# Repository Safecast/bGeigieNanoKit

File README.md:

## bGeigie Nano Kit Operating Instructions (Updated March 2025)

# Table of Contents

1.  [Introduction](#introduction)
2.  [Powering the Device On](#powering-the-device-on)
3.  [Switching Between Modes](#switching-between-modes)
4.  [Measuring Ionizing Radiation in Logging Mode](#measuring-ionizing-radiation-in-logging-mode)
5.  [Measuring Ionizing Radiation in Surface Mode](#measuring-ionizing-radiation-in-surface-mode)
    1. [Alarm](#alarm)
    2. [Data Log](#data-log)
6.  [Uploading Data to the Safecast Database With the Safecast API](#uploading-data-to-the-safecast-database-with-the-safecast-api)
7.  [Uploading Data to Other Datasets](#uploading-data-to-other-datasets)
8. [Using Safecast With Mobile Apps](#using-safecast-with-mobile-apps)
9. [Troubleshooting](#troubleshooting)
    1. [Troubleshooting the iSafecast Geiger Bot App for iOS](#troubleshooting-the-isafecast-geiger-bot-app-for-ios)
    2. [Troubleshooting the iSafecast Geiger Bot App's API](#troubleshooting-the-isafecast-geiger-bot-apps-api)
    3. [Troubleshooting Other Issues](#troubleshooting-other-issues)
        1. [Firmware](#firmware)
    4. [Cleaning](#cleaning)
10. [Warranty Information](#warranty-information)
11. [Hardware Cautions](#hardware-cautions)
12. [Resources and Support](#resources-and-support)

## Introduction
The Safecast bGeigie Nano kit is a *geo-tagged mobile sensor of ionizing radiation*. It is equipped with Internet data sharing capability and optional wireless capability. 

The term "radiation" refers to energy emitted by a source. This includes light, heat, microwaves, and other types of energy. Ionizing radiation is a type radiation that has so much energy that it removes electrons from the atoms and molecules that make up air, water, and living tissue. This activity can harm the molecules in our bodies, leading to diseases like cancer. Radiation can come from either natural or human-made sources. Natural sources include radioactive rocks, elements, and a radioactive gas called radon. Human-made sources include nuclear power plants and medical diagnostic tests, such as x-rays.

The bGeigie Nano measures alpha, beta, and gamma radiation. 

| Type | Description |
| ---- | ----------- |
| Alpha Radiation | Alpha particles are charged particles that have a large mass and charge. As a result, they don't penetrate materials as easily as other types of ionizing radiation. They also don't travel very far. |
| Beta Radiation | Beta particles are similar to electrons. They are lighter than alpha particles and travel farther, up to a few feet through air. |
| Gamma Radiation | Gamma particles are the most powerful form of ionizing radiation. They travel very far at the speed of light and penetrate most materials easily. Thick layers of concrete, lead, steel, or similar materials are required to stop gamma particles. |

The Nano's maximum operating range is about 350,000cpm, or 1mSv/h (1 millisievert per hour dose rate or 1000µSv/h microsieverts per hour). 

The Nano can be mounted on a car window, or used for static or spot radiation detection. Nano users can submit their mobile radiation measurements to Safecast, an online global mapping system developed by Safecast and MIT Media Lab. 

The Nano also records location, date, and time. The location data allows Safecast to map the measurements and understand the distribution of ionizing radiation. Safecast uses the date and time information to track how ionizing radiation concentrations change over time. The do-it-yourself kit enables customization, cost savings, and learning. 

## Powering the Device On

To turn the unit on, slide the switch at the lower right to the up position. 

The SAFECAST logo will appear on the display for approximately one second. The next start-up screen displays the name of model (bGeigie Nano), the firmware version number, battery charge level, basic settings, and the user’s name (or other customizable information).  

## Switching Between Modes

* The bGeigie Nano has two operating modes, "display" and "recording". To alternate between them, use the toggle switch at the upper right. Label on the transparent top panel: (to the right) "bq/m^2; uS/h", (to left) "log; cpm".

+ The “up” position (to the right) switches the unit into display mode (in which there is no data logging). The fields on the OLED indicate uSv/h dose-rate (Cs137), max dose-rate, dosimeter, Bq/m2 display (Cs137), time stamp, and alarm. 

+ The “down” position puts the Nano into recording mode. The OLED shows indicators for CPM and µSv/h, the number of satellites locked, altitude (meters), distance traversed (km), total duration of measurement (h:m), and time stamp (dd:hh:mm:ss). When the Nano is in recording mode, the OLED shows whether a micro-SD memory card is currently inserted. 

## Measuring Ionizing Radiation in Logging Mode

While in recording mode, the OLED display also shows a GPS lock indicator. When the device locks onto a GPS signal, it will show the number of satellites found, and a small red LED will glow. If the device isn't getting a lock, try placing it near a window for a few minutes.

The small red LED will only glow if the GPS is locked, the SD card is present, the battery has more than 10% charge left, the unit has been on for one minute, and the Geiger tube is providing a pulse. It can be dimmed by setting DIP switch #2 to "Off."

The speaker "clicks" and a small blue LED blinks with each pulse from the Geiger tube. It can be dimmed by setting DIP switch #1 to "Off."

The red LED on the GPS unit blinks every 1 second when the GPS is not locked. Once locked, it blinks every 10 seconds.

The date and time are in __UTC__ (formerly called GMT), rather than local time. The __date/time stamp__ refreshes when log data is written to the card. The LOG's file name is based on the time stamp   (e.g., 21080716.LOG).  The UTC log filename may be +/- one day off from the local date of the measurement, depending on the difference between time zones and distance from the International Date Line (IDL). The file metadata is not updated, which means the log's file creation date may appear with a default date, such as 01/01/2000. For this reason, we recommend that you sort your logs by filename instead of the date field.  When uploading a log, please enter its metadata in the required fields, and submit it for approval. 

**GPS Reset Procedure** (ver 1.3.0 and later)

To reset the GPS device: 

1) Turn off the bGeigie
2) Remove the SD card
3) Turn the bGeigie back on and leave it on for one minute 

    After approximately 10 seconds, the display will show the message "NO SD CARD/GPS Reset." Note that powering the unit on without the SD card will cause an error and **re-initialize the unit, including the GPS controller**.

4) Turn the device off again
5) Insert the SD card

## Measuring Ionizing Radiation in Surface Mode

Use surface mode to detect surface contamination. Removing the Nano from its case while in surface mode can increase the Nano's ability to detect alpha and beta radiation.

1. Remove the Nano from its case (with or without the rubber liner). Use both thumbs to push the unit in and then swivel it out. When you reinsert the Nano into the case later on, you can do it either above or inside the removable rubber liner.

While in uSv/Bq mode, the display also shows the peak dose rate (in uSv/h), total accumulated dose (in uSv), and CPM. 

The mode switch sets the bGeigie Nano into "Log Mode" (switch down "log cpm"). In Log Mode, the largest area of the display ("the big numbers") shows the count rate in CPM, and data will be written to the SD card.  In "Survey Mode" (switch up "Bq/m2 uSv/h"), the main part of the display will show the dose rate in microsieverts per hour.

- To measure the uSv dose rate accurately, put the Nano in the case, hold it 1m above the ground, tilt it around 45 degrees, and then wait for approximately one minute for a stable reading.

- To measure bQ accurately, take the Nano out of the case, keep it within 5cm to 1cm from the surface, and wait approximately one minute for a stable reading. Then, read the value on the second line in Bq/m2. The Nano will emit a speaker sound to aid in finding hotspots.

- The dose rate is based on the assumptions that the Nano is in its case; it is about 1 meter (3ft) away from any object or surface; any gamma rays are of moderate energy (600~700KeV); and the unit has met the previous conditions for at least one minute.

- Also in Survey Mode, the second line on the display ("the small numbers") will rotate through several other values. One of those will be Bq/m2. That is only a locally displayed interpretation of the data, and requires very different conditions to be correct: the Nano is _out_ of its case and held 1cm (~half inch) from a surface contaminated with radio cesium. This usage probably only works in Fukushima and Chernobyl.

### Limitations  

The grid on the pancake sensor is only useful when you remove the unit from the case to look for surface contamination. The grid itself has a very small shielding effect, mostly for alpha/beta and weak gamma radiation. The effect is minimal, and can be ignored.

When averaging readings from two different Nanos, you should only compare long-term counting (e.g. number of counts for 10 minutes).
 
### Alarm
- A speaker "clicks" and a small blue LED “Count” blinks with each pulse from the Geiger tube. It can be dimmed by setting DIP switch #1 to "Off."
- A small Red LED “Log/Alarm” flickers on pulse, and remains lit on alarm. It will only glow if the GPS is locked, the SD card is present, the battery has more than 10% charge left, the unit has been on for one minute, and the Geiger tube is providing a pulse. It can be dimmed by setting DIP switch #2 to "Off."
- The Piezo buzzer may not loud enough for all users. There are solder pads available on the Nano main board for an optional audio-out connector that can be used to connect an amplifier or sound recorder to get louder clicks, if desired.

### Data Log

In recording mode, the data log file writes to the micro-SD card. A key to the fields in the Data Log is available in the [bGeigie library README.md by fakufaku](https://github.com/Safecast/SafecastBGeigie). 

The data is formatted similarly to the NMEA sentences that GPS uses. It begins with a dollar sign ($) and ends with an asterisk (*). A checksum follows the star.

>Radiation Data Sentence: This is the basic message containing the geo-located radiation measurement.

>EXAMPLE:

>$BNRDD,300,2012-12-16T17:58:31Z,30,1,116,A,4618.9612,N,00658.4831,E,443.7,A,5,1.28*6D

**KEY**

| Field | Description | Example|
| ----- | ----------- | ---- |
| Header   | the device model header | Mini=BMRDD, Nano=BNRDD, NX=BNXRDD |
| Device ID | the device serial number | 300 |
| Date  | the date, formatted according to the ISO-8601 standard, usually in UTC | 2012-12-16T17:58:31Z |
| Radiation 1 minute  | the number of pulses given by the Geiger tube in the last minute | 30 |
| Radiation 5 seconds  | the number of pulses given by the Geiger tube in the last 5 seconds | 1 |
| Radiation total count   | the total number of pulses recorded since startup |  116  |
| Radiation count validity flag  | 'A' indicates the counter has been running for more than one minute, and the one-minute count is not zero. Otherwise, the flag is 'V' (void) | A |
| Latitude | as given by GPS; the format is ddmm.mmmm, where dd is decimal degrees and mm.mmmm is decimal minutes |  4618.9612 |
| Hemisphere |  'N' (north), or 'S' (south) | N |
| Longitude | as given by GPS; he format is dddmm.mmmm where ddd is decimal degrees and mm.mmmm is decimal minutes | 00658.4831 |
| East/West | 'W' (west) or 'E' (east) from the Prime Meridian | E |
| Altitude |  the altitude (above sea level), as given by the GPS, in meters | 443.7 |
| GPS validity | 'A' = Available or OK, 'V' = Void or invalid | A |
| Number of satellites | the number of satellites used by the GPS | 5 |
| HDOP | the Horizontal Dilution of Precision (HDOP), or relative accuracy of the horizontal position | 1.28 |
|Checksum |  | *6D |

*(For possible updates, see the current [README.md](https://github.com/Safecast/SafecastBGeigie/blob/master/README.md) in the technical GitHub repository)*

The data log file name is comprised of three parts: The DID number, the month the log was initiated, and the day the log was initiated. For example, "21080716.LOG" is the data log for unit 2108 from 16 July. Due to space constraints, the file date property is 01/01/2000. However, every line has UTC time date stamp reading.  The log file name may appear to be a day off due to time zone differences.

A data log or section begins with several comment lines, which begin with hash signs (#).

EXAMPLE:

>\# NEW LOG

>\# format=1.2.9nano

>\# deadtime=on

>$BNRDD,2108,2013-12-06T13:03:58Z,22,2,115,A,3145.7607,N,03510.1975,E,734.90,V,3,908*64

One of the comment lines contains the deadtime. [Deadtime](http://en.wikipedia.org/wiki/Dead_time) is "the time after each event during which the system is not able to record another event."  You can find the *ENABLE_LND_DEADTIME compensation formula* in the [bGeigieNano.ino master repository](https://github.com/Safecast/bGeigieNanoKit/blob/master/src/bGeigieNano.ino). 

### Uploading Data to the Safecast Database With the Safecast API

Your device is designed to submit data to the Safecast database through the Safecast API. To enable data submission, you’ll need to obtain an API key. The key is a credential that gives you access to the API, much like a username and password give you access to an email account.

You can [register on the Safecast site](https://api.safecast.org/en-US/users/sign_up) to get an API key. 

You can learn about how the Safecast API works by visiting the [API documentation](https://api.safecast.org/).

### Uploading Data to Other Datasets

Nano data can be submitted to other radiation mapping datasets. For example, the free [Geiger Bot iOS app](https://sites.google.com/site/geigerbot/) allows you to upload data to servers other than the [Safecast API dataset](https://api.safecast.org/). To do so, you'll need to configure the app with the details of your device, the particular sensor, data format, connection, and other information.  

### Using Safecast With Mobile Apps 

The official (currently not availble)[Safecast app for iOS](https://itunes.apple.com/us/app/safecast/id571167450?mt=8) brings our extensive dataset of radiation measurements to your mobile device, and provides a full toolset to help you perform measurements with your own instrument such as a Geiger or scintillation counter (not included). The app functions as a virtual Geiger counter, allowing you to see your location on a map while displaying radiation readings that have been taken nearby. The app is currently for iOS only. 

In addition, the Safecast Drive app [Android](https://github.com/Safecast/bGeigie-Drive) enables you to:

- Connect with your bGeigieNano (if you have the [bGeigeCast](https://bgeigiezen.safecast.jp/store-2/bgeigiecast-build-for-bgeigienano/) module installed), record data, and upload the data to Safecast directly, without removing your MicroSD card
- Access previous logs and update their status

**Common Issues**

1. Wrong cable - A "null modem" cable that swaps wires internally may cause problems. The cable should be straight/passthrough.
2. Input voltage too high - Interferes with the audio route and the audio engine's watchdog timer.
3. Mic-ground in the cable not shorted correctly - The app will report an audio route change to "Headphones" on the console. The audio route required for a line input cable is "Headset."

>>Nick Dolezal is working hard on the new version of the Safecast app (which will allow on demand refreshing of the map data) decided to whip up these alternate visualizations of the Safecast data. These maps show the frequency of samples taken – NOT READINGS OF THOSE SAMPLES – just showing how often a specific place has been measured. In this example, a location (like Fukushima) that has been measured repeatedly would show hot. Thought this was a really interesting look at the work Safecast has done over the last 2+ years

#### Troubleshooting the iSafecast Geiger Bot App's API

On the main numeric display of the app, you can tap on the top part of the screen to show detailed log messages containing information on connection attempts, and which input device is selected. If successful, the API upload will return HTTP 201 CREATED.

**Verify Input**

1. Tap the min/max arrow button in the lower-right hand corner of the map to resize it into a small window. The interface will display fixed buttons at the bottom, and four possible display screens at the top. These four screens are "Main Numeric Display," "CPS/CPM graph," "Audio input monitor graph," and "Map."

2. Tap the "<" button next to the white page dots under the map. The audio input monitor will appear.

3. Verify that the counts from the Onyx appear and that they're correct. The black line represents the input. The stationary red line represents the threshold the input volume must exceed for it to be counted. The black line will appear blue when it has been counted as a pulse.

If you're unable to verify input, you may have a defective serial cable. A "Geiger Pulse" setting on the Onyx of other than the default value of 6 may also cause problems. 

4. Configure the App's Settings

a. Tap the "Settings" icon on the fixed button panel (the machine gear). Scroll to the bottom of the list and select "Safecast."
b. Enter your API key. Change the upload interval as desired, but do not change the Safecast device back to Nano. 

#### Troubleshooting Other Issues

If you experience problems with the display, check all solder joints carefully to verify that you haven't missed a joint, or that you don't have a cold solder joint. These issues can cause the display to act unpredictably.

You can report bugs and other issues at the [issues page](https://github.com/Safecast/bGeigieNanoKit/issues) of the Safecast GitHub repository. Volunteer users report problems and bugs in the devices discussion group. 

##### Firmware
* For the current version of the firmware, see the the .hex file in the [bGeigieNanoKit repository](https://github.com/Safecast/bGeigieNanoKit).

* To learn how to update the firmware of the Fio via FTDI, see the ["How to Update the Firmware" page](https://github.com/Safecast/bGeigieNanoKit/wiki/How-to-Update-the-Firmware) of this wiki.

### Cleaning

To clean the unit:

1. Remove the Nano from the case. Never wet the Nano's interior. 
2. Use a soft brush and air blower on the Nano, carefully. A vacuum may be another option (electronics labs use unheated air blowers for dusting off parts.)
3. Rinse the liner in clean water, if necessary. 
4. The case may be rinsed with a clean, slightly damp microfiber cloth. 
5. Turn the screen display off and wait until it's cool before wiping the LEDs. Wipe the screen using light pressure.  Use clean, lint-free cotton, microfiber cloths or low-lint wipes. 

### Warranty Information

For warranty information, email [contact@safecast.org](contact@safecast.org). 

**Calibration** 

“The sensor is pre-calibrated. The calibration of the unit for Bq for Cs assumes the grid is in front of the pancake. The difference is around 5%. For gamma only, the grid has a negligible effect on the measured value.

The uSv/h conversion from CPM is calibrated assuming the grid is on the tube. As all Safecast measurements are done with the pancake WITH grid, please keep the grid on the tube. The grid itself will not block alpha or beta radiation, but will reduce the sensitivity slightly, as the grid covers a small portion of the sensor. In practice, the difference with and without grid will be around 4-5% for a beta source, and less for a gamma source, according to bGeigie Nano user Jam.

The software we have preloaded on the device takes the sensor type into account and calibrates readings for Cs137. All bGeigie Nanos have the same configuration and can be compared against one other. A bGeigie Nano's calibration should never change, unless the device is broken. 

### Hardware Cautions

- The Pelican micro case is shockproof and water-resistant. However, it is not waterproof and it cannot be used underwater. Condensation can build up inside the case, due to temperature differences. While this condensation will evaporate with time, you can also remove it by opening the unit and drying it with fiber-free cloth. 

- Do not use the unit outside of its water-resistant case with wet hands, in the rain, or close to a dripping tap. 

- The Micro-SD cannot be read through a USB port. Use a micro-SD card reader instead.

**Battery Cautions:** 

Charge the unit with the mini-USB cable. The yellow LED will dim once the unit is fully charged. A full charge takes 5-6 hours. The bGeigie Nano runs approx 35-40 hours on a full charge in recording mode. 

The main battery indicator is the icon at the bottom right of the display. The percent of battery charge appears on the startup screen.

**NEVER charge the bGeigie while the unit is on.** The power MUST be turned OFF before charging to avoid permanent damage to the charge circuit. 

+ Replace a broken battery (that has a detached wire) with one that has the same rating (2000mAh 3.7V Lithium Polymer (Li-Po, Li-Poly). The Nano charge circuit may overheat if you use a larger battery.

+ A Li-Po battery can be hazardous if the mylar membrane is punctured. Please handle batteries carefully! 

**SENSOR Cautions:**

Although the Nano sensor inside its closed Pelican micro-case is well protected from shock and pressure transients, sudden changes in pressure (such as slamming a car door) may damage the sensor. The pressure inside the tube is very low, and the membrane is under constant tension from atmospheric pressure. Being at altitude *reduces* the strain on it. Because the membrane is mica (basically extremely thin glass), it is low-density and very brittle. A sharp shock can shatter it, and it will pop if something pokes it. 

- To avoid damage to the pancake sensor, NEVER touch the membrane! 

**Onyx Hardware Precautions:**

To keep the Onyx™ in good condition, handle it with care, and observe the following precautions:

- Do not contaminate the Onyx™ by touching it to radioactive surfaces or materials. Instead, hold it just above the surface that is suspected of contamination to take readings. 

- Do not leave the Onyx™ in temperatures over 122° F (50° C), or in direct sunlight for extended periods of time. 

- If the surface of the mica on your pancake detector becomes scratched or loses its coating, avoid making measurements with the detector window in direct sunlight, as this could affect the readings. 

- Do not put the Onyx™ in a microwave oven. It cannot measure microwaves, and you may damage it or the oven. 

#### Resources and Support

- [Nano catch-all landing page](https://safecast.org/bgeigie-nano/)

- [Safecast website](https://safecast.org/) - articles, news, notices, API uploads, crowdsourced radiation data and maps, and more

- [Safecast Devices Discussions and Support group](https://groups.google.com/forum/?hl=en#!forum/safecast-devices)

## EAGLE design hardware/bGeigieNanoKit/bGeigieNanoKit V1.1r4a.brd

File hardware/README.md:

# HW development for bGeigieNanoKit has moved
## New V1.0r4 boards eagle files are in bGeigieNanoKit v1.0r4 folder 
## Older development can be found here [SafecastEagleHW] (https://github.com/Safecast/SafeCastEagleHW)

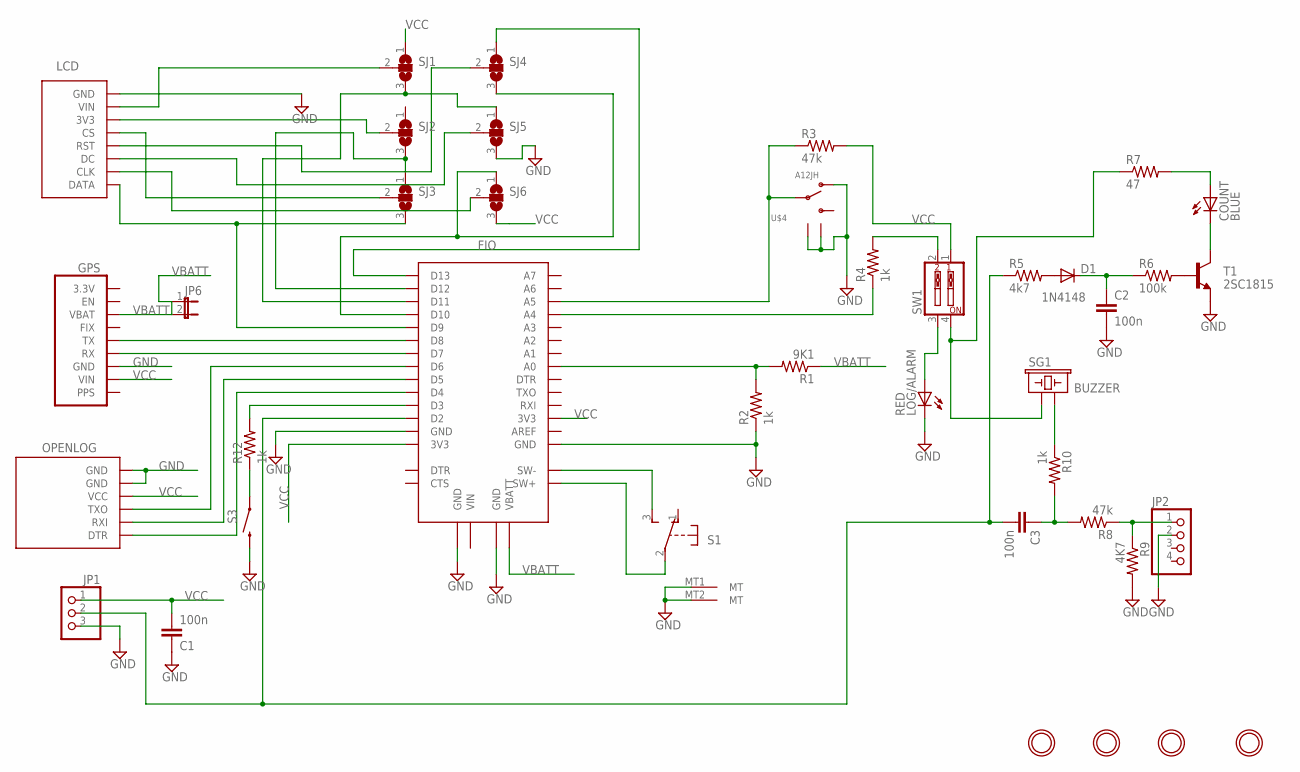
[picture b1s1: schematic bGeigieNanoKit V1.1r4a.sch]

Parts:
C1, C2, C3: 100n; C025-024X044
COUNT: BLUE; LED3MM
D1: 1N4148; DO35-7
FIO: FIO_SOCKETBOT; FIO_V23_SOCKET_BOT
GPS: ULTIMATE_GPSTOP; ULTIMATE_GPS_V3_TOP
JP1: PINHD-1X3/90; 1X03/90
JP2: HEADER-1X4ROUND; 1X04_ROUND
JP6: JUMPER-2SMD-NC; SJ_2S
LCD: SSD1306_128X64_V2_LCD1.3IN_LEVER; SSD1306_128X64_1.3IN_LCD_LEVER
LOG/ALARM: RED; LED3MM
OPENLOG: OPENLOG
R1: 9K1; 0207/10
R2, R4, R10, R12: 1k; 0207/10
R3, R8: 47k; 0207/10
R5: 4k7; 0207/10
R6: 100k; 0207/10
R7: 47; 0207/10
R9: 4K7; 0207/10
S1: S1; EG1206
S3: SWITCH-MOMENTARY-2PTH; TACTILE-PTH
SG1: BUZZER; BUZZER-12MM
SJ1, SJ2, SJ3, SJ4, SJ5, SJ6: SJ2W; SJ_2
SW1: SW_DIP-2; EDG-02
T1: 2SC1815; TO92-ECB
U$4: A12JH; A12AH
U$6, U$7, U$8, U$9: MOUNTINGHOLE3.0THIN; MOUNTINGHOLE_3.0_PLATEDTHIN

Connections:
GND: C1.1, C2.2, FIO.JP1$2 (GND), FIO.JP2$1 (GND), FIO.JP5$1 (GND), FIO.JP6$1 (GND), GPS.JP1$3 (GND), GPS.U$8$P$1 (GND), GPS.U$9$P$1 (GND), JP1.3, JP2.2, LCD.JP1$8 (GND), LCD.U$23$P$1 (GND), LCD.U$26$P$1 (GND), LOG/ALARM.K (C), OPENLOG.JP1$5 (GND), OPENLOG.JP1$6 (GND), R2.1, R9.2, S1.MT1 (MT), S1.MT2 (MT), S3.3 (2), SJ5.3, T1.E, U$4.P$1, U$4.P$4 (GND), U$4.P$5 (GND)
unnamed: FIO.JP1$10 (D9), LCD.JP1$1 (DATA), SJ3.3
unnamed: FIO.JP1$11 (D10), SJ4.3, SJ6.1
unnamed: FIO.JP1$12 (D11), SJ1.3, SJ5.1
unnamed: FIO.JP1$13 (D12), SJ2.3, SJ3.1
unnamed: FIO.JP1$14 (D13), SJ4.1
unnamed: FIO.JP1$9 (D8), GPS.JP1$5 (TX)
unnamed: FIO.JP1$8 (D7), GPS.JP1$4 (RX)
unnamed: FIO.JP1$7 (D6), OPENLOG.JP1$3 (TXO)
unnamed: FIO.JP1$6 (D5), OPENLOG.JP1$2 (RXI)
unnamed: FIO.JP1$5 (D4), OPENLOG.JP1$1 (DTR)
unnamed: FIO.JP5$7 (A0), R1.2, R2.2
unnamed: FIO.JP7$2 (SW+), S1.2
unnamed: FIO.JP7$1 (SW-), S1.3 (S)
unnamed: FIO.JP5$12 (A5), R3.1, U$4.P$2
unnamed: LOG/ALARM.A, SW1.3
unnamed: R4.2, SW1.2
unnamed: C3.2, FIO.JP1$3 (D2), JP1.2, R5.1
unnamed: COUNT.A, R7.2
unnamed: R12.1, S3.1
unnamed: COUNT.K (C), T1.C
unnamed: R10.1, SG1.- (2)
unnamed: C3.1, R8.2, R10.2
unnamed: JP2.1, R8.1, R9.1
unnamed: D1.A, R5.2
unnamed: C2.1, D1.C, R6.1
unnamed: R6.2, T1.B
unnamed: FIO.JP1$4 (D3), R12.2
unnamed: LCD.JP1$7 (VIN), SJ1.2
unnamed: R7.1, SG1.+ (1), SW1.4
unnamed: FIO.JP5$11 (A4), R4.1
unnamed: LCD.JP1$6 (3V3), SJ2.2
unnamed: LCD.JP1$5 (CS), SJ3.2
unnamed: LCD.JP1$4 (RST), SJ4.2
unnamed: LCD.JP1$3 (DC), SJ5.2
unnamed: LCD.JP1$2 (CLK), SJ6.2
VBATT: FIO.JP2$2 (VBATT), GPS.JP1$7 (VBAT), JP6.1, JP6.2, R1.1
VCC: C1.2, FIO.JP1$1 (3V3), FIO.JP5$3 (3V3), GPS.JP1$2 (VIN), JP1.1, OPENLOG.JP1$4 (VCC), R3.2, SJ1.1, SJ6.3, SW1.1

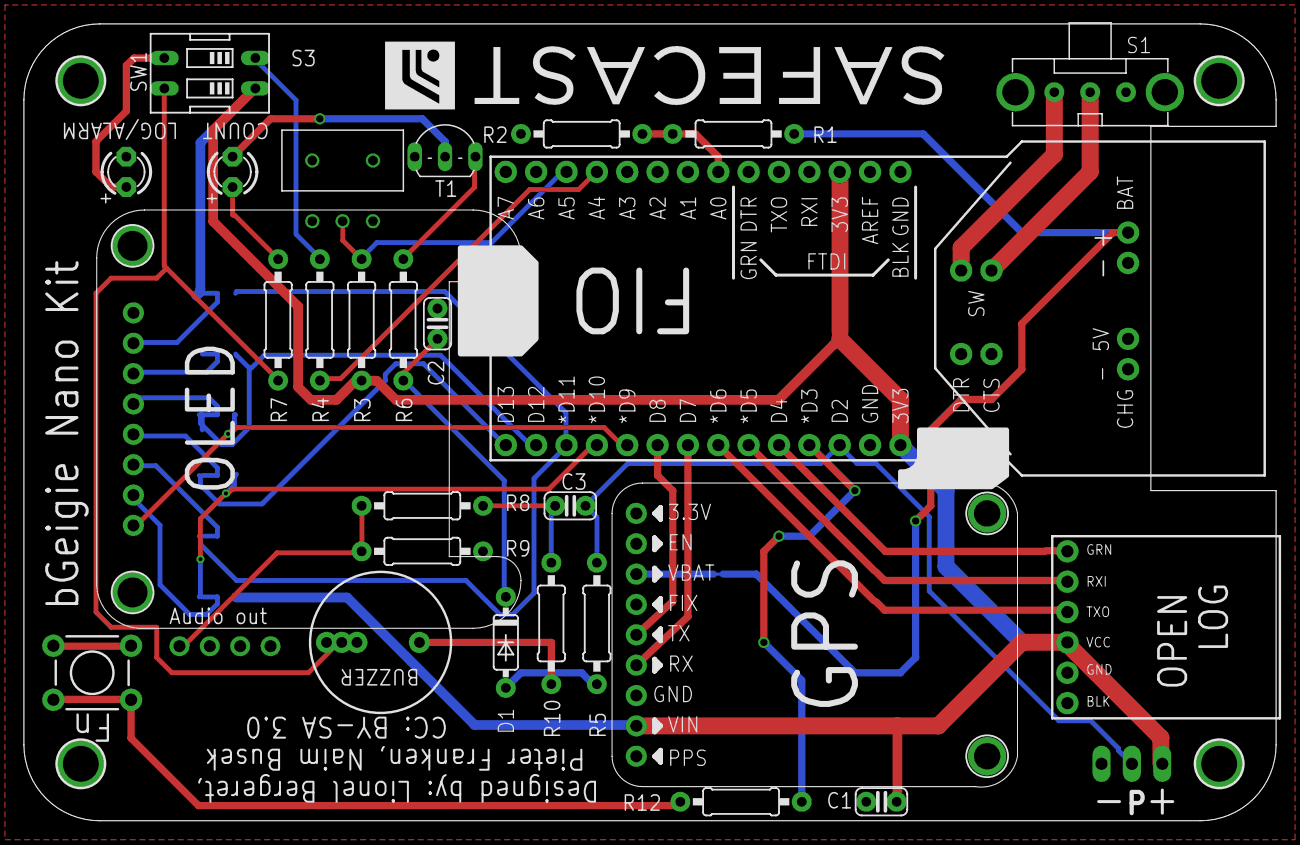
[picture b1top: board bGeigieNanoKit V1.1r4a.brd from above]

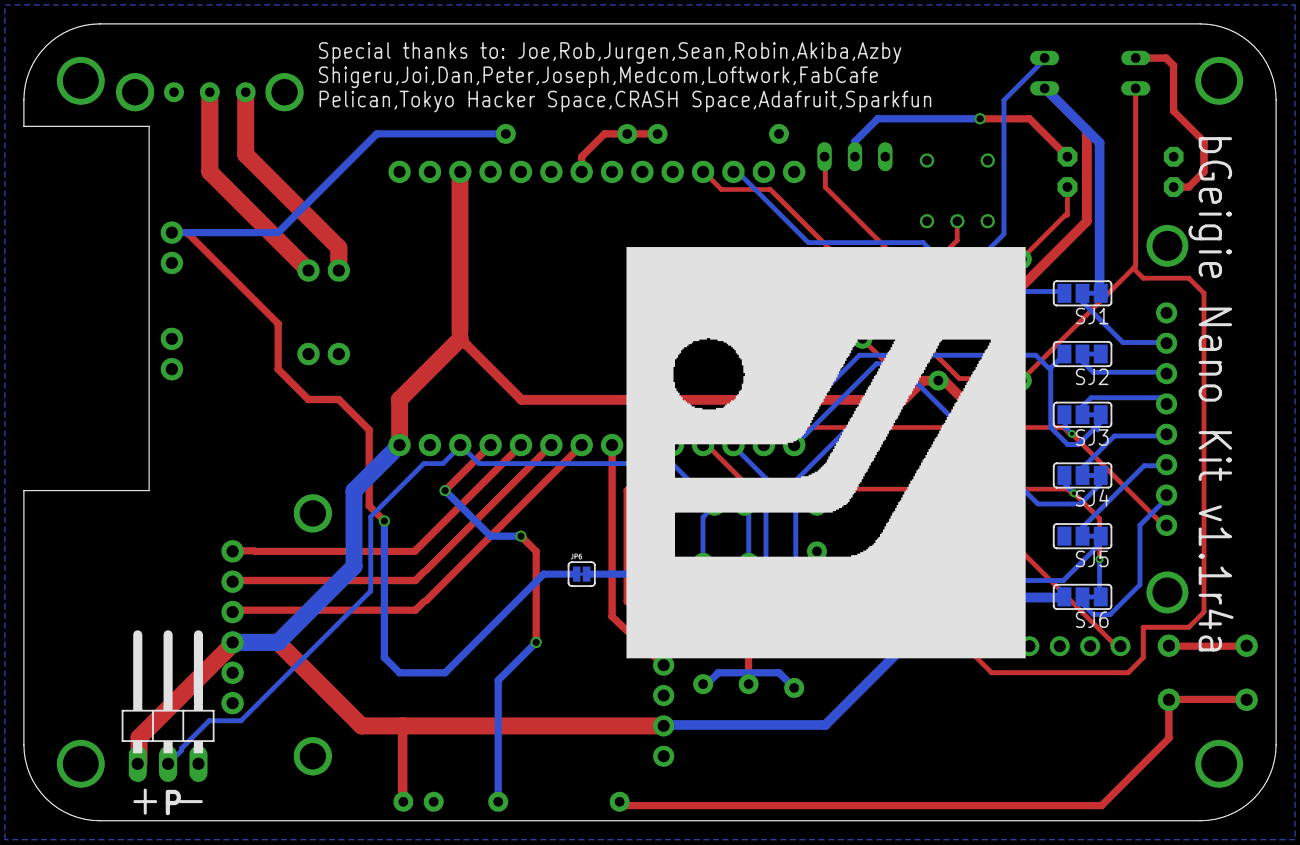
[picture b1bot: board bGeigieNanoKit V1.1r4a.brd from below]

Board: 2 copper layers, 104.8 x 66.7 mm, 42 parts (10 on the bottom side), 38 nets.

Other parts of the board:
U$1: SAFECAST_LOGO4
U$5: SAFECAST_LOGO2

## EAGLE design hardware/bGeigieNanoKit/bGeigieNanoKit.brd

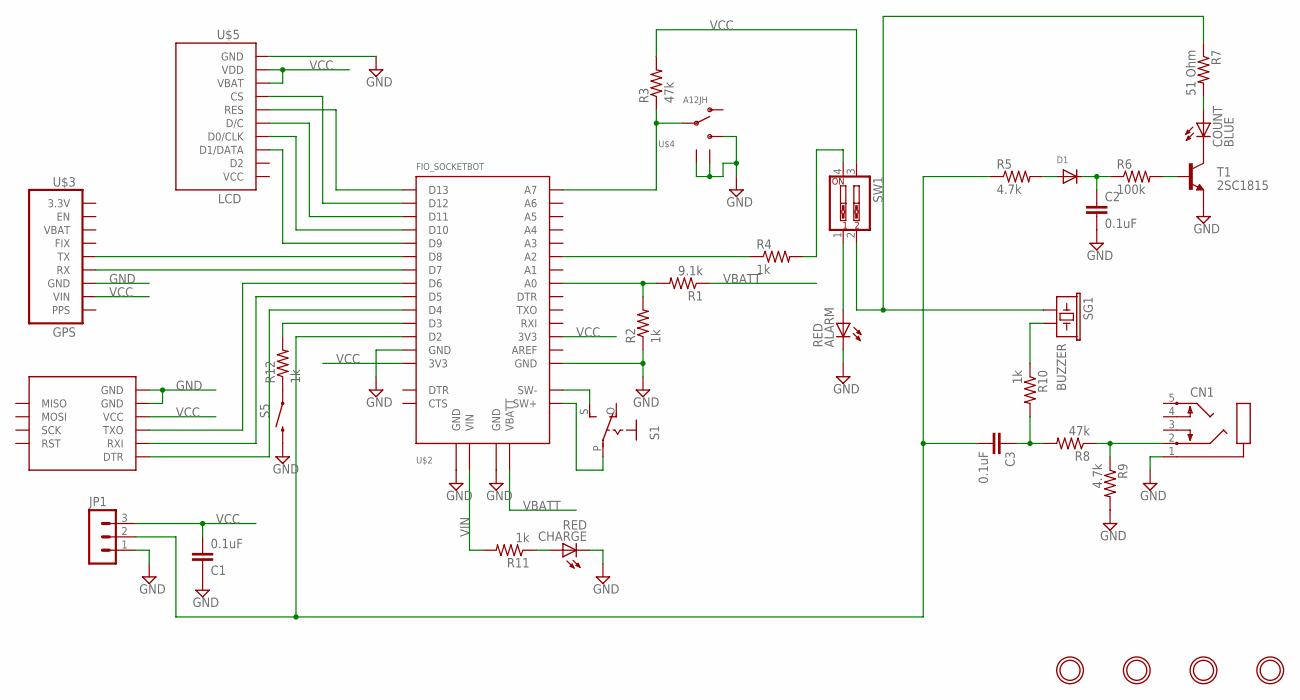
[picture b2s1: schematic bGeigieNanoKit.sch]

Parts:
ALARM: RED; LED3MM
C1, C2, C3: 0.1uF; C050-024X044
CHARGE: RED; LED3MM
CN1: AUDIO_STEREOJACK; STX3100
COUNT: BLUE; LED3MM
D1: DIODEDO-1N4148; DO-1N4148
JP1: MA03-1
R1: 9.1k; 0207/10
R2, R4, R10, R11, R12: 1k; 0207/10
R3, R8: 47k; 0207/10
R5, R9: 4.7k; 0207/10
R6: 100k; 0207/10
R7: 51 Ohm; 0207/10
S1: EG1218S; EG1218
S5: SWITCH-MOMENTARY-2PTH; TACTILE-PTH
SG1: BUZZER; BUZZER-12MM
SW1: SW_DIP-2; EDG-02
T1: 2SC1815; TO92-ECB
U$1: OPENLOG
U$2: FIO_SOCKETBOT; FIO_V23_SOCKET_BOT
U$3: GPS; ULTIMATE_GPS_V3_TOP
U$4: A12JH; A12AH
U$5: LCD; SSD1306_128X64_LCD_MIN
U$6, U$7, U$8, U$9: MOUNTINGHOLE3.0THIN; MOUNTINGHOLE_3.0_PLATEDTHIN

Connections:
GND: ALARM.K (C), C1.1, C2.2, CHARGE.K (C), CN1.1, JP1.1, R2.1, R9.2, S5.3 (2), T1.E, U$1.JP1$5 (GND), U$1.JP1$6 (GND), U$2.JP1$2 (GND), U$2.JP2$1 (GND), U$2.JP5$1 (GND), U$2.JP6$1 (GND), U$3.JP1$3 (GND), U$3.U$8$P$1 (GND), U$3.U$9$P$1 (GND), U$4.P$3, U$4.P$4 (GND), U$4.P$5 (GND), U$5.P0\$10 (GND)
unnamed: U$2.JP1$10 (D9), U$5.P0\$3 (D1/DATA)
unnamed: U$2.JP1$11 (D10), U$5.P0\$4 (D0/CLK)
unnamed: U$2.JP1$12 (D11), U$5.P0\$5 (D/C)
unnamed: U$2.JP1$13 (D12), U$5.P0\$7 (CS)
unnamed: U$2.JP1$14 (D13), U$5.P0\$6 (RES)
unnamed: U$2.JP1$9 (D8), U$3.JP1$5 (TX)
unnamed: U$2.JP1$8 (D7), U$3.JP1$4 (RX)
unnamed: U$1.JP1$3 (TXO), U$2.JP1$7 (D6)
unnamed: U$1.JP1$2 (RXI), U$2.JP1$6 (D5)
unnamed: U$1.JP1$1 (DTR), U$2.JP1$5 (D4)
unnamed: R1.2, R2.2, U$2.JP5$7 (A0)
unnamed: S1.P, U$2.JP7$2 (SW+)
unnamed: S1.S, U$2.JP7$1 (SW-)
unnamed: R3.1, U$2.JP5$14 (A7), U$4.P$2
unnamed: R4.1, U$2.JP5$9 (A2)
unnamed: ALARM.A, SW1.1
unnamed: R4.2, SW1.4
unnamed: C3.2, JP1.2, R5.1, U$2.JP1$3 (D2)
unnamed: COUNT.A, R7.2
unnamed: R12.1, S5.1
unnamed: R7.1, SG1.+ (1), SW1.2
unnamed: COUNT.K (C), T1.C
unnamed: R10.1, SG1.- (2)
unnamed: C3.1, R8.2, R10.2
unnamed: CN1.2, R8.1, R9.1
unnamed: D1.A, R5.2
unnamed: C2.1, D1.C, R6.1
unnamed: R6.2, T1.B
unnamed: CHARGE.A, R11.1
unnamed: R12.2, U$2.JP1$4 (D3)
VBAT: U$3.JP1$7 (VBAT)
VBATT: R1.1, U$2.JP2$2 (VBATT)
VCC: C1.2, JP1.3, R3.2, SW1.3, U$1.JP1$4 (VCC), U$2.JP1$1 (3V3), U$2.JP5$3 (3V3), U$3.JP1$2 (VIN), U$5.P0\$1 (VCC), U$5.P0\$8 (VBAT), U$5.P0\$9 (VDD)
VIN: R11.2, U$2.JP6$2 (VIN)

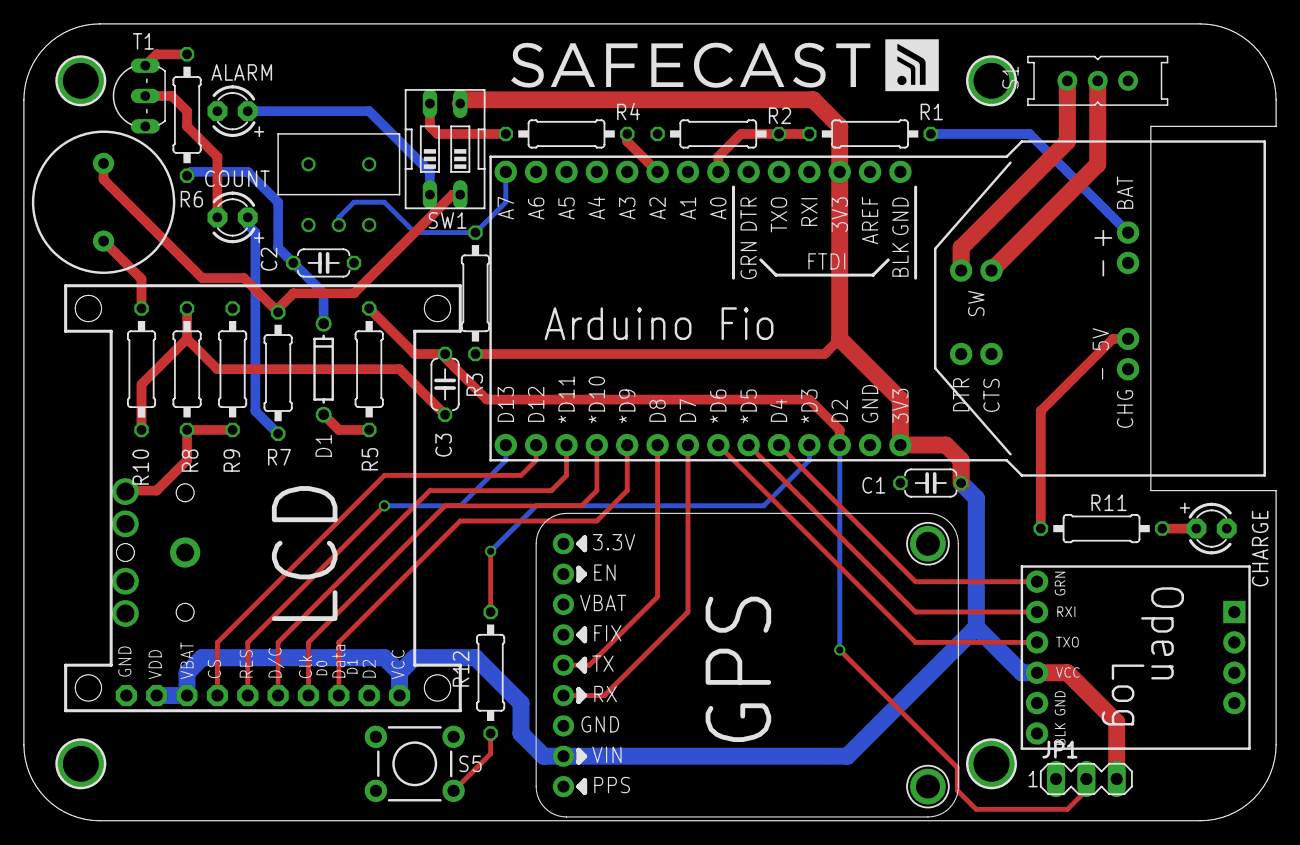
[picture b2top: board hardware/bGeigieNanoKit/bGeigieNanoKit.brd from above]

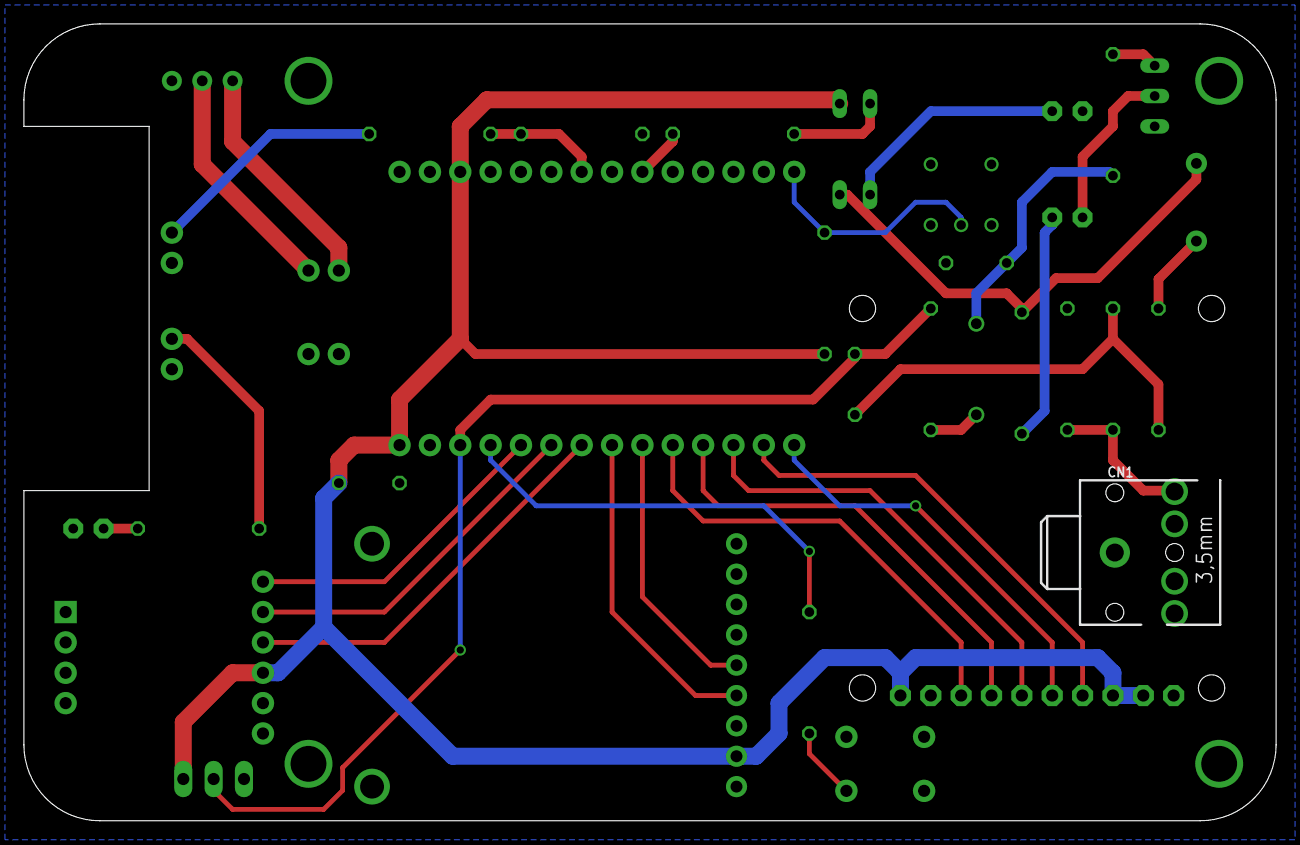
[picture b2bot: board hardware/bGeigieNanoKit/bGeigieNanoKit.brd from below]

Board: 2 copper layers, 104.8 x 66.7 mm, 36 parts (2 on the bottom side), 34 nets.

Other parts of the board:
U$10: SAFECAST_LOGO1

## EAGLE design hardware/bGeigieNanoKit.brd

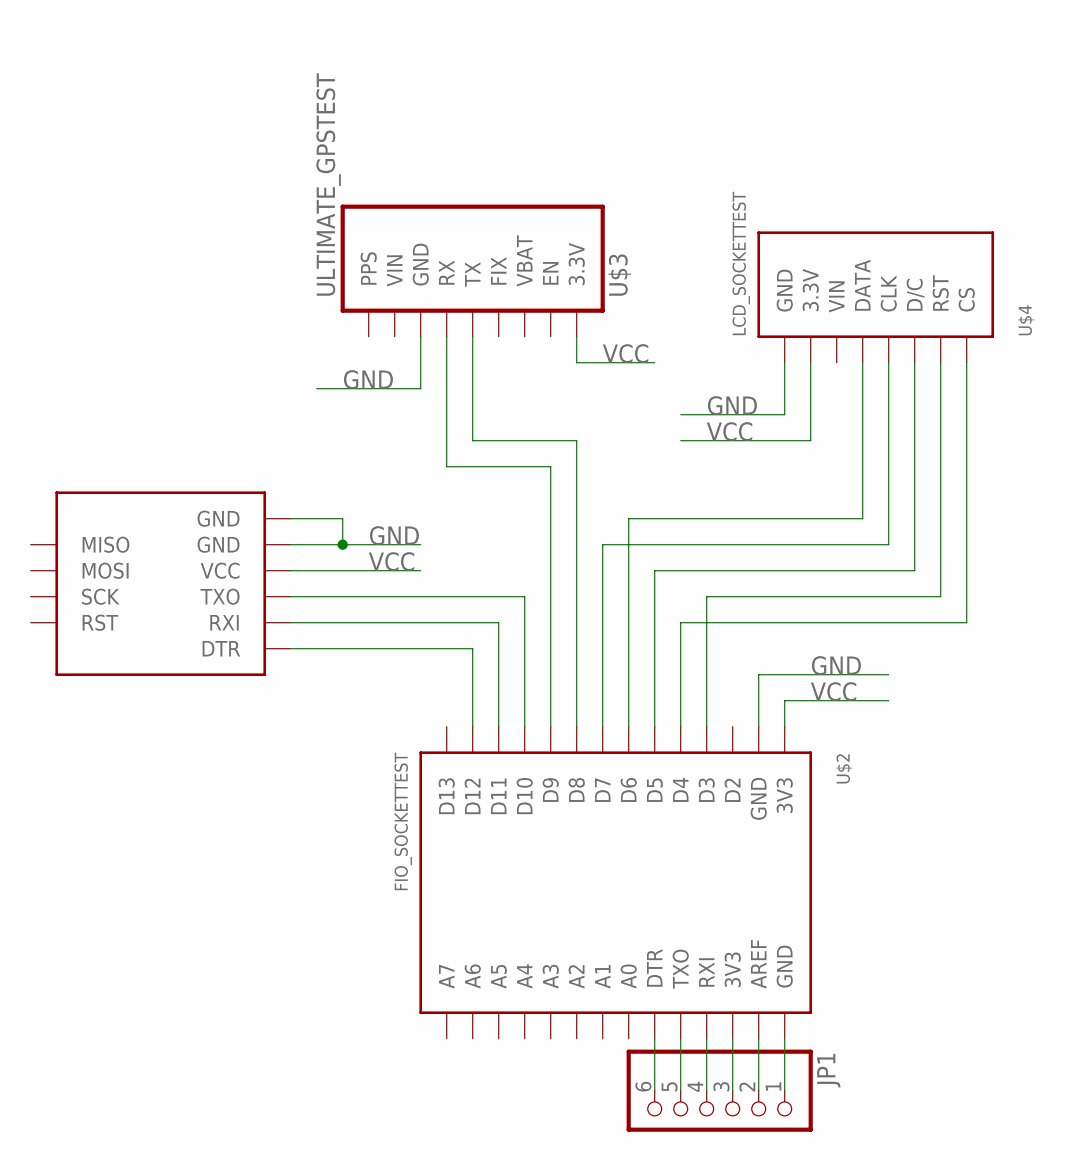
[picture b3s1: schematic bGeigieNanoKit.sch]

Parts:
JP1: PINHD-1X6; 1X06
U$1: OPENLOGTEST; TEST_OPENLOG
U$2: FIO_SOCKETTEST; TEST_FIO
U$3: ULTIMATE_GPSTEST; TEST_GPS
U$4: LCD_SOCKETTEST; TEST_LCD

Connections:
GND: U$1.JP1$5 (GND), U$1.JP1$6 (GND), U$2.JP1$2 (GND), U$3.JP1$2 (GND), U$3.U$8 (GND), U$3.U$9 (GND), U$4.8 (GND), U$4.U$2 (GND), U$4.U$3 (GND), U$4.U$4 (GND), U$4.U$5 (GND)
unnamed: U$1.JP1$1 (DTR), U$2.JP1$13 (D12)
unnamed: U$1.JP1$2 (RXI), U$2.JP1$12 (D11)
unnamed: U$1.JP1$3 (TXO), U$2.JP1$11 (D10)
unnamed: U$2.JP1$10 (D9), U$3.JP1$3 (RX)
unnamed: U$2.JP1$9 (D8), U$3.JP1$4 (TX)
unnamed: U$2.JP1$7 (D6), U$4.5 (DATA)
unnamed: U$2.JP1$8 (D7), U$4.4 (CLK)
unnamed: U$2.JP1$6 (D5), U$4.3 (D/C)
unnamed: U$2.JP1$4 (D3), U$4.2 (RST)
unnamed: U$2.JP1$5 (D4), U$4.1 (CS)
unnamed: JP1.1, U$2.JP5$1 (GND)
unnamed: JP1.2, U$2.JP5$2 (AREF)
unnamed: JP1.3, U$2.JP5$3 (3V3)
unnamed: JP1.4, U$2.JP5$4 (RXI)
unnamed: JP1.5, U$2.JP5$5 (TXO)
unnamed: JP1.6, U$2.JP5$6 (DTR)
VBAT: U$3.JP1$6 (VBAT)
VCC: U$1.JP1$4 (VCC), U$2.JP1$1 (3V3), U$3.JP1$8 (3.3V), U$4.7 (3.3V)
VIN: U$3.JP1$1 (VIN), U$4.6 (VIN)

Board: 2 copper layers, 5 parts (1 on the bottom side), 19 nets, no tracks yet.

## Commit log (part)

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2012-06-05 Initial version 0.1
2012-06-05 Fix latitude and longitude output format (6 digits)
2012-06-05 Add copyright notice
2012-06-05 Fix typos
2012-06-05 Update sample log
2012-06-06 Add assembly and sample log
2012-06-06 Add overview diagram
2012-06-06 First running version (more than 15 hours using a 850mAh battery)
2012-06-07 Add estimated power consumption and log duration
2012-06-07 Fix table rendering
2012-07-02 Add global pin definition and Mini Pro support (software serial for GPS instead of XBee socket)
2012-07-04 Add log entry checksum
2012-07-04 Update log format to make it compatible with bBeigie Classic or Mini (speed is removed)
2012-07-05 Update OpenLog usage to create log file only when GPS is ready (with id and date in the filename)
2012-07-06 Add EEPROM device id support (USE_EEPROM_ID) to be used with bGeigieConfigBurner
2012-07-06 Update to latest changes (for Fio and SOFTGPS enabled)
2012-07-07 Update GPS processing interval and EEPROM id (read/write)
2012-07-10 Add sleep mode support (Read GPS data for 1 second then update bgeigie log and finally sleep for 4 seconds)
2012-07-11 Fix log file name generator (don't generate if date is null)
2012-07-13 Add support for TinyGPS raw mode Update sleep to standby mode
2012-07-23 Add OLED SSD1306 support (+ reduce memory usage)
2012-07-23 Optimize memory usage from 1294 bytes to 1172 bytes (use PROGMEN and PSTR)
2012-07-24 Enable DGPS and SBAS on MTK3339 GPS module. Add heading information on OLED screen (cardinal).
2012-09-23 Add first Nano kit software version
2012-09-23 Add pelican reference
2012-09-25 Fix minor typos
2012-09-25 Add openlog component to diagram
2012-09-26 Update OLED screen to Adafruit 128x32 091" SPI
2012-09-27 Update GND and VCC pin assigment comment
2012-09-28 Update pin connections
2012-10-01 Configuration file for bGeigieNano (available keys are cpm_factor, id and dose)
2012-10-02 Add assembly summary sheet
2012-10-02 Always printout the log on serial (BluetoothBee use case)
2012-10-04 Small code cleanup (remove unnecessary code)
2012-10-04 Add ENABLE_EEPROM_DOSE support
2012-10-05 Add small identifier to the displayed gps status
2012-10-05 Switch Nano device id to 4 digits
2012-10-05 Update log filename to handle 4 digits device id
2012-10-05 Add config support to sensor type, shield, height and mode
2012-10-07 Latest Nano build version 1.0.2 (2012-10-07 16h30 GMT+9)
2012-10-10 Enable deadtime compensation and optimize display
2012-10-11 Add geigie type switch support Update battery indicator (3.5v to 4.3v)
2012-10-11 Add sensor type/shield/mode definitions
2012-10-11 Add dead-time compensation setting
2012-10-11 Add country name configuration support
2012-10-11 Add alarm level support in configuration
2012-10-12 Add 100m coordinates truncation option
2012-10-12 Add OLED Adafruit libraries (Safecast logo and reduce fonts)
2012-10-16 Update documentation with libraries
2012-10-17 updated hardware files using auto generated footprints
2012-10-19 updated library footprints with single/double sided options. preliminary component placement on board to verify fit.
2012-10-29 increasing width of outlines. moving outlines place layers
2012-10-29 resize board to be better fit in case. did inital pass at routing.
2012-10-31 cleaned up final routing
2012-10-31 smashing all parts and moving labels to be visable adding current limit resistor for charge led add lables to leds
2012-11-06 adding v2 version of the board with a single LCD
2013-01-07 adding configuration for bGeigie PCB kit
2013-01-09 V 1.03 (Rob)
2013-01-11 resolving pin conflict and fixing selector switch and vbatt inputs
2013-01-18 changing huge bitmap to const so compiler can actually put it in progmem
2013-01-18 adding check for serial rx buffer size
2013-02-12 adding HW readme with current location of development
2013-02-12 cleaning up the text
2013-02-12 cleaning up wording
2013-02-12 creating an acknowledgements section
2013-02-12 cleaning up the wording
2013-02-16 File format fix
    Frmat fields was not correct according to the file format in Github
2013-02-16 Changed R5 and R9 to 4.7 k
    For decreasing the load on the IRover output to prevent lower CPM count.
2013-03-04 Error message Low Battery in Caps and reversed
2013-03-05 XGeigie alarm setup
    XGeigie mode alarm setup taken from CPM level of SAFECAST.TXT
    Second splash screen Mode and Alarm info (Mode info not working yet)
2013-03-06 LED alarm mode and battery status change.
    Alarm LED blicks in XGeigie mode if threshold is crossed. It now blick
    every 5 seconds.
    Some adjustments for the startup % battery status to have 100% when
    full changed
2013-03-21 Typo and Display two more digit in "over 1K CPM" mode
2013-03-21 Update Version for over 1k display bug fix
2013-03-25 Note: "RGB red is cutting, RGB green is engraving, black is editable text for the serial (needs to be expanded and turned to RGB green before cutting)"
2013-04-01 Display units small if over 1kCPM
    In bGiegieMode over 1k CPM display switches to smaller unit to allow
    more digits to be displayed.
    In xGiegieMode over 5k CPM display switches to smaller unit to allow
    more digits to be displayed.
2013-04-01 Higher than 100uS/h fix
2013-04-04 V1.1.4 fix high CPM
2013-04-04 V1.1.6 switched digit after decimal point in low and high rreading mode xGeigieNano
2013-04-12 V1.1.7 NS SD Card error message
    Displays "NO SD CARD" message if no SD card is present at startup. Also
    disables the the LOG light in bGeigiemode.
2013-04-16 V1.1.9 reverse display in xGeigie mode not working
    removed some mistaken test code.
2013-04-28 V1.2.0 NO GPS error reversed
    V1.2.0 NO GPS error reversed display in bGiegie Mode
2013-05-02 Config and Safecast parameters chnage
    a parameter to adjust the disaply for time zone - can you add a task on
    Github to implement this. This could also be used to set the date/time
    for the LOG file so it makes more sense
2013-05-06 V1.2.2
    Fixed xGeigie display mode
2013-05-09 Revert "V1.2.3"
    This reverts commit 668ce3222101854a211a2feaaed39e447b06664e.
2013-05-09 V1.2.3
    Switch height/distance and running time.
2013-06-03 V1.2.5 Cleanup some old code and test for 10K
2013-06-15 added placement guide jpd's
2013-06-16 Added small components pictures
2013-07-05 V1.2.6
    Fixed number sateltites
2013-07-10 Fix warning issues
2013-07-14 V.1.2.7
    nbstat fixed again
2013-07-23 the trick pics
    Additional tricks for the manual
2013-08-07 V1.2.8
    Changed serial baudrate to 14400 for communications with BLEbee (can
    reset if needed back to 9600)
2013-08-10 Improving comment and reordiring the code.
2013-10-08 edited more pictures for the manual
2013-10-21 Update measurement display for large CPM > 10000
2013-10-21 Move some string to .text segment
2013-10-28 Fix imprecision issue with coordinates parsing
2013-10-28 V1.3.0
2013-11-05 remove .DS_Store
2013-11-05 V1.3.0 (update)
2013-11-06 Merge branch 'master' of https://github.com/Safecast/bGeigieNanoKit
    Conflicts:
    NanoConfig.h
    bGeigieNano.hex
    bGeigieNano.ino
2013-11-06 V1.3.1
    Added space to message
2013-11-11 V1.3.2
    Really 1.2.8 with added functionality of 1.3.0. to gt GPS reset
    working. GPS can be reset by removing SD card on startup. A message
    will be display "No SDcard/. GPS reset". After power down and power up
    the GPS module will be completly reset and will take time to lock for
    the first time.After that locking should acure fast.
2013-11-13 HEX for 1.3.2
2013-12-07 V1.3.4
    Updated display code and setup baud rate serial for 9600.
2014-01-07 Revert "Changed the log line format to comply with bGeigieMini standard."
    This reverts commit 4fbbef94e25989889c8bba96a1c2e9804324ab9b.
2014-01-08 V1.3.5
    Added the log changes made by Robin
2014-01-13 V1.3.4 Mac Hex Uploader
    V1.3.4 Uploader for the hex file to a Mac.
    1- Unzip
    2- Connect bGeigieNano with FTDI cable
    3- Double click in the app. (maybe need authorisation . No Apple ID
    creator)
    4- restart bGeigieNano.
2014-01-30 Nano lasercut files
    .ai file with cutting instructions. Delete text before sending to
    lasercutter.
2014-05-08 Revised manual images May 2014
    5 revised photos showing audio connector as optional; one new photo
    showing new 1200mAh battery.
2015-04-08 wait until date fixes
    In some condition, uninitialized date will be
    used, resulting in creating invalid filename of
    year 2000.
2015-04-08 fix return after datetime process finished.
2015-04-08 calculate the date time first
2015-10-17 Updated README file in hardware
2016-02-14 ASCII version for development. Runs on Arduino IDE 1.6.6. Much lower memory. Displays battery status in %.
2017-02-03 Started to port for ReadBear Duo board.
2017-03-21 Use bgeigie integrated pin config.
2017-03-21 Modified NanoSetup to work with SD rather than openlog. Added tests sketch.
2017-03-21 Added some now missing math functions (radians, degrees) in TinyGPS, also use float version of math func rather than double.
2017-03-21 Correct i2c address for screen.
2017-03-22 Using RGB led to indicate status of last SD write (log not ready / done / failed). Added commented code for soft shutdown
2017-03-24 Added board and schematic board v1.1r4 x png files.
2017-05-24 Fixed V1.1r4a board for deleted trace and added gerber files. Added editable templates for CS6.
2017-05-24 Added editable CS6 files
2017-08-24 update licenses.
2017-11-24 Added the uploader
2017-12-05 5 seconds display if cpm is higher then alarm
2017-12-06 Changed to version 4 and changed display only "^" if in high cpm scan mode
2017-12-06 Adjusted screen display for hotspot and switched logic.
2017-12-13 Moved indiction for 60s /5s to be in sync with display switching.
2018-01-03 Added fix for display 4 digits in kCPM mode
2018-01-07 added hex file
2018-02-23 Setup config file for JP
2018-06-02 Fix SDcard reading (Ray)
2018-06-04 Added uploader for mac
2018-06-04 Added Mac uploader app
2018-06-07 Added newer board files and labled hex and zip of the Mac upload application.
2018-07-30 V1.4.2 test for fix for uS/h display in hot spot mode
2018-08-02 V1.4.2 with display fix
2018-08-03 Display fix for not logging mode small display
2019-01-07 Fixed schematic for V1.1.5 board.
2019-02-05 Add files via upload
    Added missing photo
2019-03-25 Updated version and added new uploader app.
2019-03-26 Modified the header of the Mac app to reflect the correct version
2019-09-24 new file: bGeigeiNano_V1.4.3_uploader.app.zip new file: bGeigeiNano_V1.4.3_uploader.app/Contents/Info.plist
2020-11-03 Added content SAFECAST.TXT explanation
2021-01-16 Init
2021-01-18 Setting up shock sensor
2021-03-22 Added shock setup routine
2021-03-22 added shock display test
2021-04-10 Adde more code to get the shcok sensor working
2021-05-15 V1.4.9 Switched pins for shock
2021-05-21 Updated with shock sensor at D3
2021-05-22 Updated shock happend and 5 minutes delay. Shows "s" instead of 5/50
2021-05-22 Updated version numbering
2021-05-23 Disabled 5s to 60s option with switch
2021-05-24 Moved function pin from D3 to A3 or A7 (Rob and Pieter) V1.5.1
2021-06-30 Added Ray fixes
2021-06-30 Prevent lost interrupts; deal with floating point cast issues
    The way that the code was dealing with interrupts, there was a window
    in which interrupts would be lost. This change fixes that window by
    never resetting the hardware counter, and instead just allowing it
    to run continuously and then just sampling the 'difference' from
    the last time it was sampled.
    In order to do the necessary "wraparound" processing for the hardware
2021-07-07 fixed up warning
2021-07-20 Addtional fixes
2021-07-20 Updated version number
2021-08-02 Update with Ray fixes.
2021-08-02 Updated to version 1.5.3
2021-09-18 Cleaned up and added CAD files (PDF)
2021-10-24 V1.4.4 fix by Ray
2021-10-24 Updated the Mac 32 bit uploader app for V1.4.4a (fix for 1.4.4)
2021-10-25 Updated Mac uploader and firmware.hex in .pio filder sttructure
2022-09-23 Updated history
2022-10-05 Updated V1.5.5
2022-10-07 Added old boards info
2022-10-07 Update version number
2022-11-10 Fixed type in the history notes
2023-01-04 one more place changed copyrights
2023-07-05 Fixed display bug on shock sensor part of the code
2023-07-05 Added 7 days reste function
2023-08-14 Added log files for tetsing
2024-10-07 Add files via upload
    Added Xloader for Windows to flash the hex file, Original from https://github.com/binaryupdates/xLoader
2025-01-27 Working with VSCode
2025-01-27 Update copy right year
2025-09-23 Add files via upload
    new SSD1306 library and housekeeping
2025-09-24 always show GPS status

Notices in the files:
parts and their libraries:
microbuilder: This work is placed in the public domain, and may be freely used for commercial and non-commercial work with the following conditions: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
SparkFun: Licensing: CC v3.0 Share-Alike You are welcome to use this library for commercial purposes.
